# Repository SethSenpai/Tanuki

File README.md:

# Tanuki 40% keyboard
### The trash panda 40%

#### What is the Tanuki?
The Tanuki is a 40% keyboard that uses a split spacebar design to comfortably switch between layers. The design goal for the Tanuki was to make a staggered 40% keyboard out of materials I had lying around in my workshop.
This is also where it gets its name. A Tanuki or [Japanese raccoon dog](https://en.wikipedia.org/wiki/Japanese_raccoon_dog) is also known as a trash panda on the internet, which I felt was a fitting name for something build out of leftover materials.

#### Why open source?
The reason I am not doing a group buy or anything else of the sort is because I want people to experiment. To try different things with a keyboard that is not going to ruin your bank account if you get it wrong the first time.
I feel that running a group buy or outright producing this keyboard will take away the experimental nature of the project. I want people to take what I designed and mold it into something that is theirs. To use this more as a platform of departure rather than a guide to follow. Ok, I will stop rambling about design philosophy now.

You are of course more than welcome to run your own group buy!
**If you intend to use this design for commercial use, please go right ahead!**

#### Features
+ A staggered design.
+ Extremely small bezel.
+ Interactive RGB underglow that shows what layer you're on.
+ Buttons to turn off or reconfigure your underglow.
+ The ability to modify and adapt the keyboard to your wildest dreams! (and perhaps learn new skills doing so!)

#### How do I use the Tanuki?
The Tanuki works by having a split spacebar design. Holding either side of the spacebar will shift the keyboard to a different layer giving you access to the characters on that layer. 
Please note that while playing video games you should switch to the game layer. Some games to not handle the spacebar hold interaction well and will eat your inputs. (not good when playing your high adrenaline games)
Switching to the game layer will remove the hold function from the spacebar, fixing the problem.

#### Where is %this_key% on the keyboard?
The Tanuki has 3 layers, if the key you want is not on any of these layers you will have to dive into the firmware and put it somewhere you like!

**Base layer:**

**Up layer:**

**Down layer:**

**Game layer: (sort of a bad name I know more like arrow layer ah well)**

#### I'm sold, where do I go from here?
Visit the `Assembly and Parts` folder to get an idea of how to construct a Tanuki. Otherwise start by making a case by going to the `Case` folder. From there you can decide to handwire your Tanuki or have a pcb made. After that comes assembly and firmware! 

#### More pictures please?

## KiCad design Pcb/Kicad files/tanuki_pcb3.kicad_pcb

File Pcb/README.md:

# Tanuki 40% keyboard
### PCB files

#### What do I do with this?
+ If you just want to have a pcb made. Use the `Tanuki-gerber.zip` file and upload this to your pcb manufacturer of choice.
+ The files in the `Tanuki-gerber-files` folder mirror the files in the zip and this folder can be used to check if all the files that your manufacturer needs are there.
+ Otherwise modifications or new gerber files can be made by using the files found in the `Kicad files` folder.

Special thanks to [StormPegy](https://github.com/Stormpegy) for making the pcb.

#### Picture of a manufactured pcb

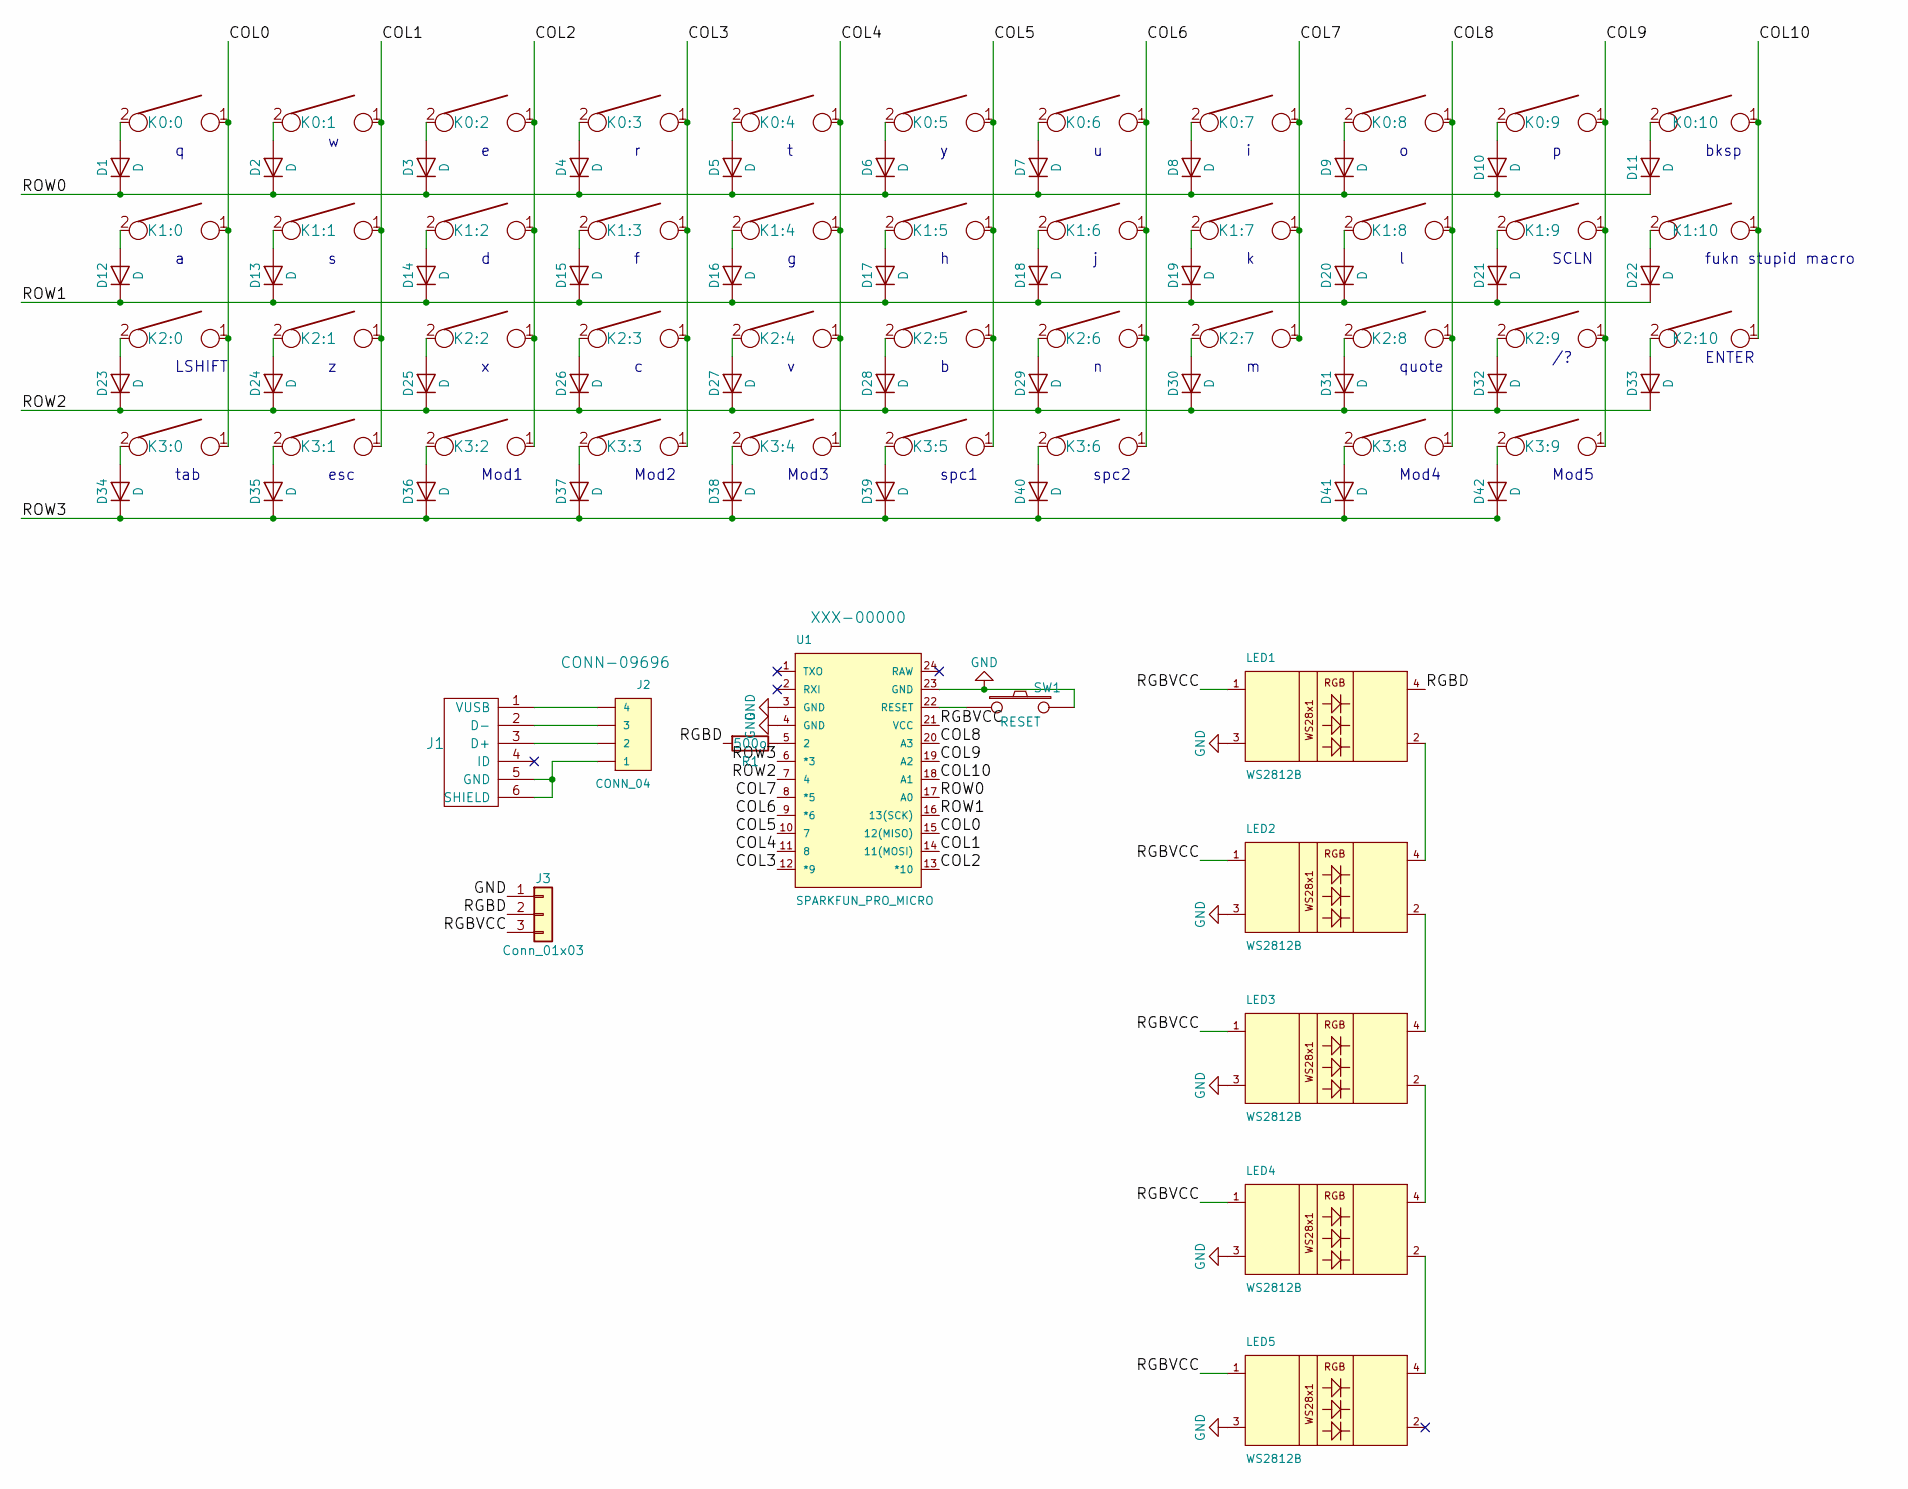
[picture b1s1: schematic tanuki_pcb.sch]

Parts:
D1, D2, D3, D4, D5, D6, D7, D8, D9, D10, D11, D12, D13, D14, D15, D16, D17, D18, D19, D20, D21, D22, D23, D24, D25, D26, D27, D28, D29, D30, D31, D32, D33, D34, D35, D36, D37, D38, D39, D40, D41, D42: D; D_SOD123_axial
J1: USB_mini_micro_B; 54819-0519fix2
J2: CONN_04; Pin_Header_Straight_1x04_Pitch2.54mm
J3: Conn_01x03; Pin_Header_Straight_1x03_Pitch2.54mm
K0:0, K0:1, K0:2, K0:3, K0:4, K0:5, K0:6, K0:7, K0:8, K0:9, K1:0, K1:1, K1:2, K1:3, K1:4, K1:5, K1:6, K1:7, K1:8, K1:9, K1:10, K2:1, K2:2, K2:3, K2:4, K2:5, K2:6, K2:7, K2:8, K2:9, K3:1, K3:3, K3:4, K3:5, K3:6, K3:8: KEYSW; MX_PCB_100H
K0:10, K2:10, K3:0, K3:2, K3:9: KEYSW; MX_PCB_125H
K2:0: KEYSW; MX_PCB_150H
LED1, LED2, LED3, LED4, LED5: WS2812B; LED_WS2812B-PLCC4
R1: 500o; R_0603_HandSoldering
SW1: RESET; TACTILE_SWITCH_SMD_6.0X3.5MM
U1: SPARKFUN_PRO_MICRO

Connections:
/COL0: K0:0.1, K1:0.1, K2:0.1, K3:0.1, U1.15 (12(MISO))
/COL1: K0:1.1, K1:1.1, K2:1.1, K3:1.1, U1.14 (11(MOSI))
/COL2: K0:2.1, K1:2.1, K2:2.1, K3:2.1, U1.13 (*10)
/COL3: K0:3.1, K1:3.1, K2:3.1, K3:3.1, U1.12 (*9)
/COL4: K0:4.1, K1:4.1, K2:4.1, K3:4.1, U1.11 (8)
/COL5: K0:5.1, K1:5.1, K2:5.1, K3:5.1, U1.10 (7)
/COL6: K0:6.1, K1:6.1, K2:6.1, K3:6.1, U1.9 (*6)
/COL7: K0:7.1, K1:7.1, K2:7.1, U1.8 (*5)
/COL8: K0:8.1, K1:8.1, K2:8.1, K3:8.1, U1.20 (A3)
/COL9: K0:9.1, K1:9.1, K2:9.1, K3:9.1, U1.19 (A2)
/COL10: K0:10.1, K1:10.1, K2:10.1, U1.18 (A1)
/RGBD: J3.2, LED1.4 (DI), R1.2
/RGBVCC: J3.3, LED1.1 (VDD), LED2.1 (VDD), LED3.1 (VDD), LED4.1 (VDD), LED5.1 (VDD), U1.21 (VCC)
/ROW0: D1.1 (K), D2.1 (K), D3.1 (K), D4.1 (K), D5.1 (K), D6.1 (K), D7.1 (K), D8.1 (K), D9.1 (K), D10.1 (K), D11.1 (K), U1.17 (A0)
/ROW1: D12.1 (K), D13.1 (K), D14.1 (K), D15.1 (K), D16.1 (K), D17.1 (K), D18.1 (K), D19.1 (K), D20.1 (K), D21.1 (K), D22.1 (K), U1.16 (13(SCK))
/ROW2: D23.1 (K), D24.1 (K), D25.1 (K), D26.1 (K), D27.1 (K), D28.1 (K), D29.1 (K), D30.1 (K), D31.1 (K), D32.1 (K), D33.1 (K), U1.7 (4)
/ROW3: D34.1 (K), D35.1 (K), D36.1 (K), D37.1 (K), D38.1 (K), D39.1 (K), D40.1 (K), D41.1 (K), D42.1 (K), U1.6 (*3)
GND: J3.1, LED1.3 (VSS), LED2.3 (VSS), LED3.3 (VSS), LED4.3 (VSS), LED5.3 (VSS), SW1.2, U1.3 (GND), U1.4 (GND), U1.23 (GND)
unnamed: D1.2 (A), K0:0.2
unnamed: D2.2 (A), K0:1.2
unnamed: D3.2 (A), K0:2.2
unnamed: D4.2 (A), K0:3.2
unnamed: D5.2 (A), K0:4.2
unnamed: D6.2 (A), K0:5.2
unnamed: D7.2 (A), K0:6.2
unnamed: D8.2 (A), K0:7.2
unnamed: D9.2 (A), K0:8.2
unnamed: D10.2 (A), K0:9.2
unnamed: D11.2 (A), K0:10.2
unnamed: D12.2 (A), K1:0.2
unnamed: D13.2 (A), K1:1.2
unnamed: D14.2 (A), K1:2.2
unnamed: D15.2 (A), K1:3.2
unnamed: D16.2 (A), K1:4.2
unnamed: D17.2 (A), K1:5.2
unnamed: D18.2 (A), K1:6.2
unnamed: D19.2 (A), K1:7.2
unnamed: D20.2 (A), K1:8.2
unnamed: D21.2 (A), K1:9.2
unnamed: D22.2 (A), K1:10.2
unnamed: D23.2 (A), K2:0.2
unnamed: D24.2 (A), K2:1.2
unnamed: D25.2 (A), K2:2.2
unnamed: D26.2 (A), K2:3.2
unnamed: D27.2 (A), K2:4.2
unnamed: D28.2 (A), K2:5.2
unnamed: D29.2 (A), K2:6.2
unnamed: D30.2 (A), K2:7.2
unnamed: D31.2 (A), K2:8.2
unnamed: D32.2 (A), K2:9.2
unnamed: D33.2 (A), K2:10.2
unnamed: D34.2 (A), K3:0.2
unnamed: D35.2 (A), K3:1.2
unnamed: D36.2 (A), K3:2.2
unnamed: D37.2 (A), K3:3.2
unnamed: D38.2 (A), K3:4.2
unnamed: D39.2 (A), K3:5.2
unnamed: D40.2 (A), K3:6.2
unnamed: D41.2 (A), K3:8.2
unnamed: D42.2 (A), K3:9.2
unnamed: J1.1 (VUSB), J2.4
unnamed: J1.2 (D-), J2.3
unnamed: J1.3 (D+), J2.2
unnamed: J1.5 (GND), J1.6 (SHIELD), J2.1
unnamed: LED1.2 (DO), LED2.4 (DI)
unnamed: LED2.2 (DO), LED3.4 (DI)
unnamed: LED3.2 (DO), LED4.4 (DI)
unnamed: LED4.2 (DO), LED5.4 (DI)
unnamed: R1.1, U1.5 (2)
unnamed: SW1.1, U1.22 (RESET)

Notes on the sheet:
tab
esc
Mod1
Mod2
Mod3
spc1
spc2
Mod4
Mod5
quote
LSHIFT
ENTER
SCLN
bksp
fukn stupid macro

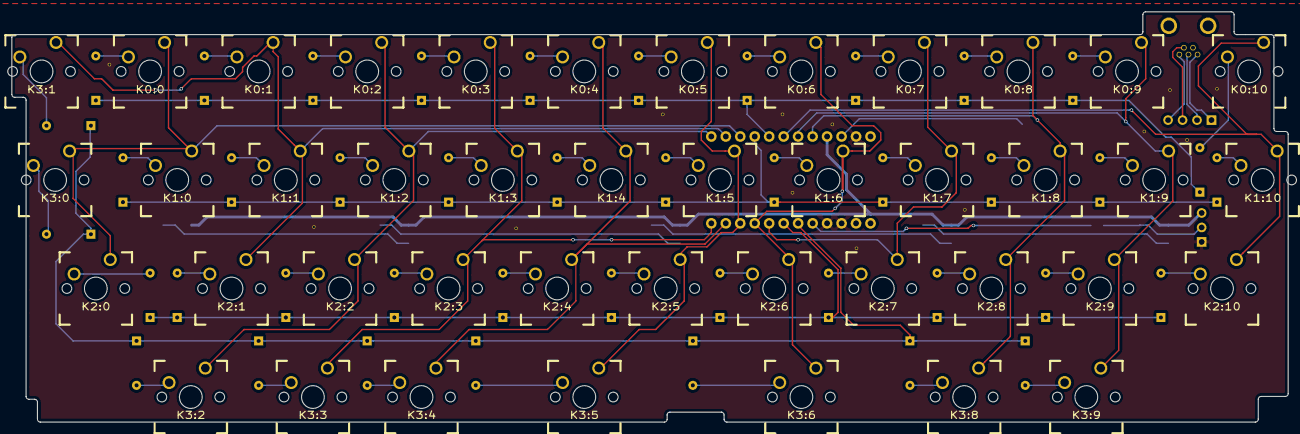
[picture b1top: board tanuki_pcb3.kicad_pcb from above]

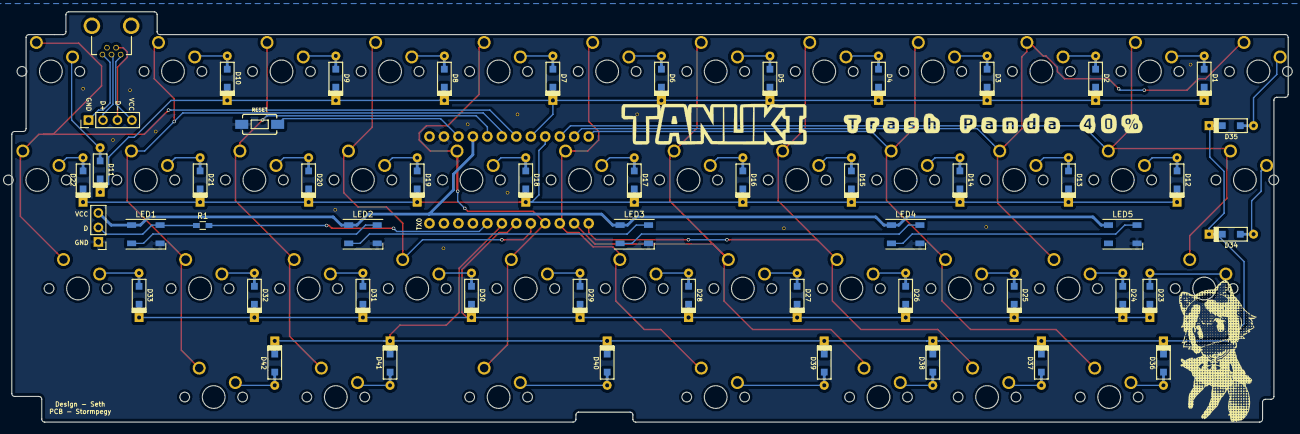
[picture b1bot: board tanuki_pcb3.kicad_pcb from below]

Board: 2 copper layers, 224.0 x 72.0 mm, 95 parts (53 on the bottom side), 70 nets.

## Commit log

2018-05-04 added readme for case folder
2018-05-04 added links to firmware readme
2018-05-04 updated firmware to comply with new qmk requirements. added glamour shots for readme
2018-05-05 added pcb files
2018-05-05 pcb stuff update
2018-05-05 picture for pcb readme
2018-05-05 added intro readme
2018-05-05 spelling error and layout
2018-05-05 update case and firmware readme
2018-05-05 more pictures
2018-05-05 added matrix image
2018-05-05 added matrix to firmware readme
2018-05-05 added assembly and pcb pictures
2018-05-05 small update
2018-05-05 added asembly instructions
2018-05-05 finished readme with tips
2018-05-05 smallthing
2018-05-05 added more lists
2018-05-06 added small firmware update to make the spacebar function better in video games.
2018-05-06 compressed glamour pictures and changed some text around
2018-05-10 small licence addition and explaination of the gamelayer interaction
2018-05-10 updated qmk link and renamed folder
2018-05-10 removed renamed folder
2018-05-10 updated contact information
2018-05-10 updated folder name in text
2018-05-11 oops
2018-07-19 updated qmk links to new documentation
2018-07-19 forgot one link
2019-07-05 added 3d files for 3d printing, updated the case readme
2019-07-05 updated readme because of spelling and grammar erros
2019-11-19 added pdf version of the pcb
2020-09-29 Added MIT license
2022-07-30 change readme to no longer require confirmation for commercial use
